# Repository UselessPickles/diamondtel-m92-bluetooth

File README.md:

# DiamondTel Model 92 Bluetooth Adapter

This is an electronics/microcontroller project for adapting a DiamondTel Model 92 Portable Cellular Telephone to work as a fully functional phone by routing calls through a modern cell phone via the Bluetooth Hands-Free Profile (HFP).

This project includes both a custom electronics circuit and custom microcontroller software.

**UPDATE**: A new version of this project is in development with custom PCBs that are completely hidden inside of the original car phone transceiver. See the [new-standalone-design branch](https://github.com/UselessPickles/diamondtel-m92-bluetooth/tree/new-standalone-design) of this project, but beware that documentation is not fully updated, and it is very much still in progress.

- [DiamondTel Model 92 Bluetooth Adapter](#diamondtel-model-92-bluetooth-adapter)
  - [About This Project](#about-this-project)
    - [TL;DR (with demo videos)](#tldr-with-demo-videos)
    - [The DiamondTel Model 92 Portable Cellular Telephone](#the-diamondtel-model-92-portable-cellular-telephone)
    - [Motivation / Goals](#motivation--goals)
    - [Project Forum Thread](#project-forum-thread)
    - [Discussion](#discussion)
    - [Documentation](#documentation)
    - [Media Coverage](#media-coverage)
  - [Basic Design](#basic-design)
    - [High Level Design Summary](#high-level-design-summary)
    - [Design Pros/Cons](#design-proscons)
  - [Compatibility](#compatibility)
    - [Vintage Mobile Phone](#vintage-mobile-phone)
    - [Paired Modern Cell Phone](#paired-modern-cell-phone)
  - [Build Your Own Bluetooth Adapter](#build-your-own-bluetooth-adapter)
  - [About the Author](#about-the-author)
  
## About This Project

### TL;DR (with demo videos)

I have an old car phone in my early 90's car. It's impossible to activate service for these old phones. I made the old car phone actually work like a real phone.

Click to view a YouTube video tour and demo of the complete car phone system with Bluetooth adapter:

You can find all videos I have created about this project in [this YouTube playlist](https://www.youtube.com/playlist?list=PLOlio4FadqvQEWHDXaJHlkvHigROk-RNV).

### The DiamondTel Model 92 Portable Cellular Telephone

The DiamondTel Model 92 Portable Cellar Telephone is a hybrid transportable/mobile (mobile, as in, "car phone") manufactured by Mitsubishi in the early 1990's. 

The phone used 1G analog cellular technology ([AMPS](https://en.wikipedia.org/wiki/Advanced_Mobile_Phone_System)), which has been discontinued in the US since 2008. As such, it is impossible to activate service for this phone. 

See the contents and README in the `telephone` directory for more details.

### Motivation / Goals

I want my DiamondTel Model 92 telephone to actually work as a phone, and not just by hacking an off-the-shelf Bluetooth headset into the phone's handset. I want the complete experience of the phone to be nearly indistinguishable from how the phone was originally intended to behave:

- Incoming calls should cause the phone to ring, and I should be able to answer incoming calls as expected (press the "SEND" button or pick up the handset).
- I should be able to place outgoing calls by dialing a number on the handset then pressing "SEND".
- The handset display should work and display all relevant information just like the original phone did.
- Sounds should be accurate to the original phone (button press sounds, ringtone, status alert sounds, etc.).
- A majority of the phone's original features should be fully functional (e.g., volume controls, call timer, quick dial presets, contacts directory with names and numbers).

### Project Forum Thread

I have documented my entire journey with this project in an [Electro-Tech-Online.com forum thread](https://www.electro-tech-online.com/threads/making-a-bluetooth-adapter-for-a-car-phone-from-the-90s.162764/).

Browse this thread if you are interested in all the technical details of how I reverse-engineerd how the DiamondTel Model 92 telephone works, how I fumbled my way through the electronics/hardware (with much appreciated assistance), and various problems I had to solve.

Subscribe to this thread if you want to be notified of significant updates about this project.

### Discussion

Do you have something to ask/say about this project? You can reach out to me in [this Gitter chat room](https://gitter.im/UselessPickles/diamondtel-m92-bluetooth).

### Documentation

There's too much information to put in one README. Most directories of this project have a README containing relevant documentation for that portion of the project. So explore the directory structure and use the READMEs to get familiar with it.

### Media Coverage

There's been a bit of media coverage of my project. Here's some links:

- [Hackaday](https://hackaday.com/2023/04/13/custom-bluetooth-adapter-brings-1990s-car-phone-back-online/)
- [Jalopnik](https://jalopnik.com/vintage-factory-car-phone-connects-to-smartphone-1850329711)
- [CarBuzz](https://carbuzz.com/news/genius-turns-30-year-old-mitsubishi-3000gt-into-a-smartphone)
- Hagerty: Piston Slap
    - [Part 1](https://www.hagerty.com/media/advice/piston-slap/piston-slap-new-tricks-for-an-old-car-phone-part-iv/)
    - [Part 2](https://www.hagerty.com/media/advice/piston-slap/piston-slap-new-tricks-for-an-old-car-phone-part-v/)
- [Japanese Nastolgic Car](https://japanesenostalgiccar.com/mitsubishi-3000gt-car-phone-functional-with-iphone-bluetooth/)
- [Hackster.io](https://www.hackster.io/news/jeff-lau-s-open-source-bluetooth-adapter-brings-a-mitsubishi-carphone-classic-back-from-the-dead-383864868529)
- [The Drive](https://www.thedrive.com/news/clever-collector-mods-mitsubishi-3000gt-car-phone-to-work-like-an-iphone)

## Basic Design

### High Level Design Summary

- A custom Bluetooth adapter connects inline between the DiamondTel Model 92 handset and transceiver.
- The transceiver provides its power supply and power on/off functionality to the Bluetooth adapter.
    - Power supply, ground, and handset power button connection is passed through the Bluetooth adapter between the handset and transceiver.
    - When the transceiver powers on, the Bluetooth adapter also powers on via the same power supply that powers the handset.
- The Bluetooth adapter takes full control of the handset.
- The Bluetooth adapter fully implements all behavior that is experienced by interacting with the handset. Much of it is a replica of (or inspired by) the DiamondTel Model 92's original behavior.
- The Bluetooth adapter communicates with the transceiver to monitor the transceiver battery level.    
- There is no direct pass-through communication between the handset and transceiver.
    - As far as the transceiver knows, it simply powers up and remains in its default idle state at all times (except for when the Bluetooth adapter requests the battery level).
- The Bluetooth adapter pairs with a modern cell phone using the Bluetooth Hands-Free Profile (HFP). This Bluetooth connection is used to:
    - Monitor/display cell service status and signal strength, etc.
    - Handle incoming calls.
    - Send outgoing calls.
    
### Design Pros/Cons

Pros:

- Plug-n-play design - no modifications to the original phone.
- No separate power supply is needed.
- Can pair with practically any modern cell phone (no separate SIM card needed).
- The vintage mobile phone has the appearance of being a completely original and functioning phone (assuming that the Bluetooth adapter is hidden, which is easy when the phone is installed in a vehicle as a car phone).
- Full control of implementing any desired behavior (within limitations of the handset display/button capabilities, and within limitations of Bluetooth HFP), including functionality that was never available/possible on the original phone (e.g., Caller ID).

Cons:

- Requires a lot of custom software to replicate original DiamondTel Model 92 functionality as faithfully as possible (but that's OK with me; I'm a software engineer, and this is fun!).
- This is not a general design that will work with a wide range of vintage mobile phones.

## Compatibility

### Vintage Mobile Phone

Because this design relies on a direct wired interface with the handset and transceiver (using proprietary connections and digital communications), it has very limited compatibility. As of now, this project is only known to work with the following vintage mobile phones:

- DiamondTel Model 92
- Mitsubishi Model 1500

### Paired Modern Cell Phone

Any modern cell phone that supports Bluetooth Hands-Free Profile (HFP) _should_ (in theory) be able to pair with the Bluetooth adapter and work properly. I have a very limited selection of phones to test with, so I can't make any guarantees.

These are the modern cell phones performed at least some basic testing with:

- Apple iPhone 8
- Apple iPhone SE
- Apple iPhone 14
- Google Pixel 3 XL

## Build Your Own Bluetooth Adapter

I don't have a complete detailed step-by-step guide, but all the information needed to build your own Bluetooth adapter should be here.

Some prerequisites:
- Soldering skills. There's a lot of soldering if you build a prototype like mine.
- Attention to detail. There are countless opportunities to make mistakes if you are not careful, and it may be a very long time and a large amount of effort before you discover that something is not working correctly.
- Basic understanding of electronics and how to use tools like a multimeter and an oscilloscope to verify your work along the way or troubleshoot when something doesn't work because you probably made a mistake while soldering everything together (I made several small mistakes while building my prototype that I had to troubleshoot and fix).
- Computer/software competency. You will need to use a variety of software tools to load configuration and code onto the Bluetooth module and the microcontroller. These are not the most user-friendly software tools.

Basic steps for building a Blutooth adapter:
1. See the `/hardware` directory README and the VeroRoute circuit layout to find all the components/parts you'll need. VeroRoute can give you a BOM list of components and quantities of most components. The README has some additional details of other items/components used in my prototype.
1. See the `/bluetooth/config` directory README for details about how to update/configure the BM62 Bluetooth module. If you use the same breadboard adapter as I did for the BM62, and you use female header sockets on your circuit, then you can easily update/configure the BM62 at any time either before or after the rest of the circuit is put together. If you want to solder the BM62 directly into your circuit, then you need to come up with a plan for how you will update/configure the BM62.
1. Build the hardware based on the information found in the `/hardware` directory/README.
1. Build the microcontroller software in the `/microcontroller/DiamondTelM92Bluetooth.X` directory and load it onto the microcontroller, using [MPLAB X](https://www.microchip.com/en-us/tools-resources/develop/mplab-x-ide) and a [PICKIT 4](https://www.microchip.com/en-us/development-tool/PG164140) or equivalent tool. Use the internet to learn how to do this if you don't already know.
1. See the `/operating_instructions` directory README for information about how to use the Bluetooth adapter.

## About the Author

I'm a software engineer with primary professional expertise in front-end web app development, but I've also played around with some basic electronics and microcontoller programming for fun. This is by far my most ambitious electronics/microcontroller project. 

The electronics side of things is my weakness, and I've relied on quite a bit of assistance from people that know electronics better than me to get this far. If you know electronics, and think I did something stupid or unnecessary in my circuit design, then you're probably right! Please file an issue against this project if you have recommendations!

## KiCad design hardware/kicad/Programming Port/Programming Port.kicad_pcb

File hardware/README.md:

# Bluetooth Adapter Hardware

This directory contains information about the hardware portion of the DiamondTel Model 92 Bluetooth adapter.

NOTE: The Bluetooth Module, Microcontroller, and Telephone all have dedicated top-level directories with relevant technical information, datasheets, and much more. This directory focuses more on combining all the components together into the bluetooth adapter hardware.

- [Bluetooth Adapter Hardware](#bluetooth-adapter-hardware)
  - [Basic Circuit Design](#basic-circuit-design)
  - [Major Circuit Components](#major-circuit-components)
    - [Microcontroller (PIC18F27Q43)](#microcontroller-pic18f27q43)
    - [Bluetooth Module (BM62)](#bluetooth-module-bm62)
    - [Hands-Free Microphone Jack (STX3120)](#hands-free-microphone-jack-stx3120)
    - [Analog Switches (MAX4619)](#analog-switches-max4619)
    - [Op Amp (NJU7031)](#op-amp-nju7031)
    - [Low-Pass Filter](#low-pass-filter)
    - [Digital Potentiometer (MCP4151)](#digital-potentiometer-mcp4151)
    - [Differential Audio Driver (INA105)](#differential-audio-driver-ina105)
    - [5V Voltage Regulator (L7805CV)](#5v-voltage-regulator-l7805cv)
    - [Negative Voltage Converter (TL7660)](#negative-voltage-converter-tl7660)
  - [Detailed Circuit Diagrams](#detailed-circuit-diagrams)
  - [Prototype Board Layout](#prototype-board-layout)
  
## Basic Circuit Design

This is a simplified component diagram of the bluetooth adapter circuit. Many details of the circuit (power, ground, voltage biasing, supporting components, etc.) are omitted for clarity of understanding the big picture of how the major components interact with each other.

[TODO]

## Major Circuit Components

This is a summary of all the major components of the bluetooth adapter circuit.

Datasheets for most components can be found in `datasheets` directory.

NOTE: Not all of these components are represented in the [Basic Circuit Design](#basic-circuit-design) diagram.

### Microcontroller (PIC18F27Q43)

This is what integrates everything together and implements all the interactive phone behavior.

See the top-level `/microcontroller` directory and the contained MPLAB project directory for more details.

### Bluetooth Module (BM62)

This handles all the Bluetooth communication with a modern cell phone, as commanded by the Microcontroller.

See the top-level `/bluetooth` directory for more details.

### Hands-Free Microphone Jack (STX3120)

This 3.5mm audio jack is used for connecting an external microphone for hands-free conversation.

The jack includes disconnect switches that are used to trigger a digital input to the MCU, indicating when
an external microphone is connected.

### Analog Switches (MAX4619)

This component is a set of 3 analog SPDT switches in one component. This is used to allow the Microcontroller to control the routing of audio:

- Choose between sending incoming voice audio or MCU-generated sounds to the Handset.
- Choose between sending the handset microphone audio or external hands-free microphone audio to the Bluetooth Module.
- Disable the microphone connection to the Bluetooth Module to temporarily "mute" the microphone while the MCU is generating sound output to the Handset.

### Op Amp (NJU7031)

This Op Amp is used to buffer the raw DAC sound output from the Microcontroller before passing it through any further circuitry.

Another is used to amplify the incoming audio from the external hands-free microphone jack.

### Low-Pass Filter

A single stage RC network is used to *partially* smooth out the 10KHz sample rate DAC audio output from the Microcontroller.

The original car phone appears to intentionally retain some high-frequency overtones in the sounds it produces. This gives the sounds a more harsh/piercing sound quality, which probably helps ensure the ringer is heard when there's an incoming call.

I similarly intentionally setup the low-pass filter to only partially smooth over the sharp corners of the DAC output. It's not an exact match to the original phone, but it sounds similar enough.

### Digital Potentiometer (MCP4151)

This digital potentiometer allows the Microcontroller to control the volume of audio output the the Handset.

### Differential Audio Driver (INA105)

A pair of INA105 precision unity gain opamps is used to produce [differential](https://en.wikipedia.org/wiki/Differential_signalling) audio output to the Handset. One is setup as unity gain, while the other is setup as inverting unity gain.

NOTE: This component requires a +5V and -5V power supply.

### 5V Voltage Regulator (L7805CV)

This voltage regulator produces a +5V power supply for the circuit. The ~12V power supply from the Transceiver is used as input.

### Negative Voltage Converter (TL7660)

This component produces a -5V power supply from the main +5V power supply. This is necessary for the [Differential Audio Driver](#differential-audio-driver-ina105).

## Detailed Circuit Diagrams

See the KiCad projects in the `kicad` directory for complete schematics and PCB layouts.

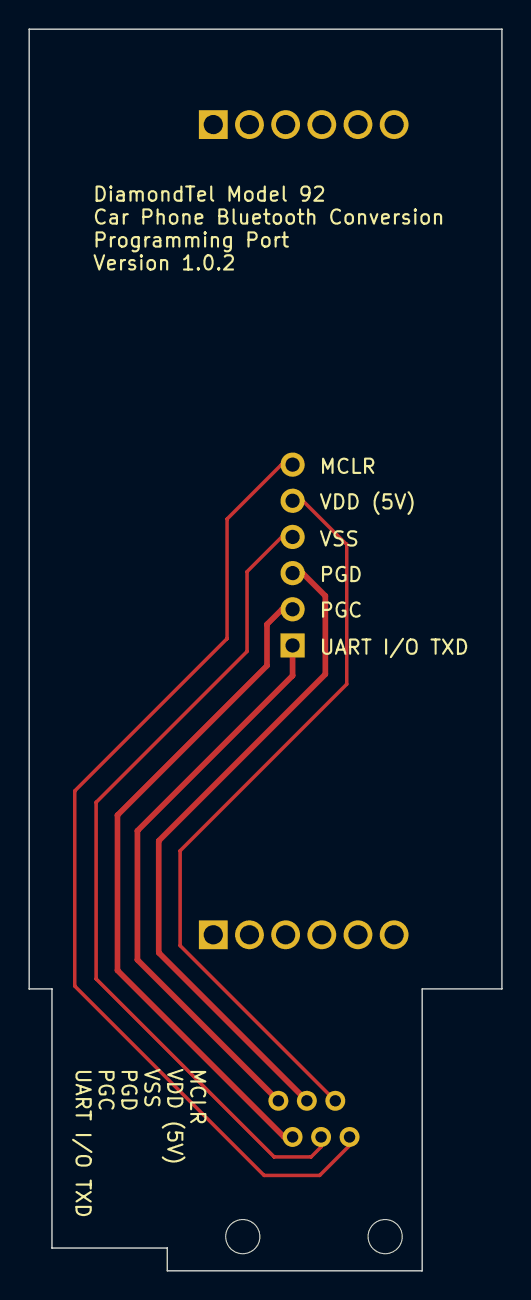
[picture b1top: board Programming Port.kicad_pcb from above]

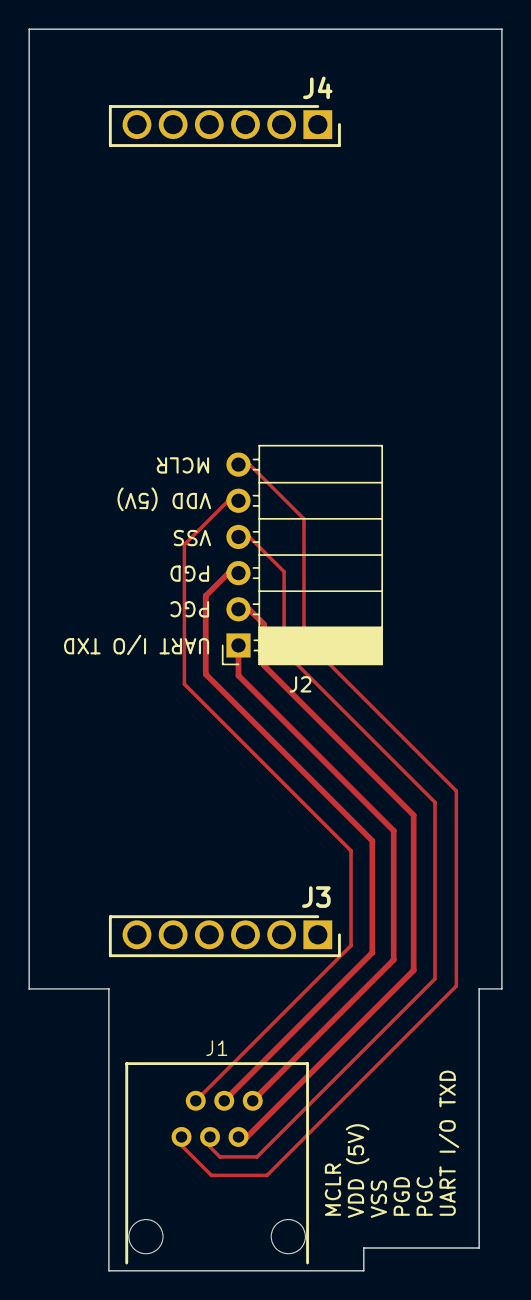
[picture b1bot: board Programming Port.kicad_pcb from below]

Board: 2 copper layers, 33.2 x 87.2 mm, 4 parts (4 on the bottom side), 6 nets.

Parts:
J1: TM5RE1-66
J2: PPTC061LGBN-RC; PinSocket_1x06_P2.54mm_Horizontal
J3, J4: PPTC061LFBN-RC; RHDR6W80P0X254_1X6_1574X254X870P_1MM_SPACER

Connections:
unnamed: J1.6, J2.1
unnamed: J1.5, J2.2
unnamed: J1.4, J2.3
unnamed: J1.3, J2.4
unnamed: J1.2, J2.5
unnamed: J1.1, J2.6

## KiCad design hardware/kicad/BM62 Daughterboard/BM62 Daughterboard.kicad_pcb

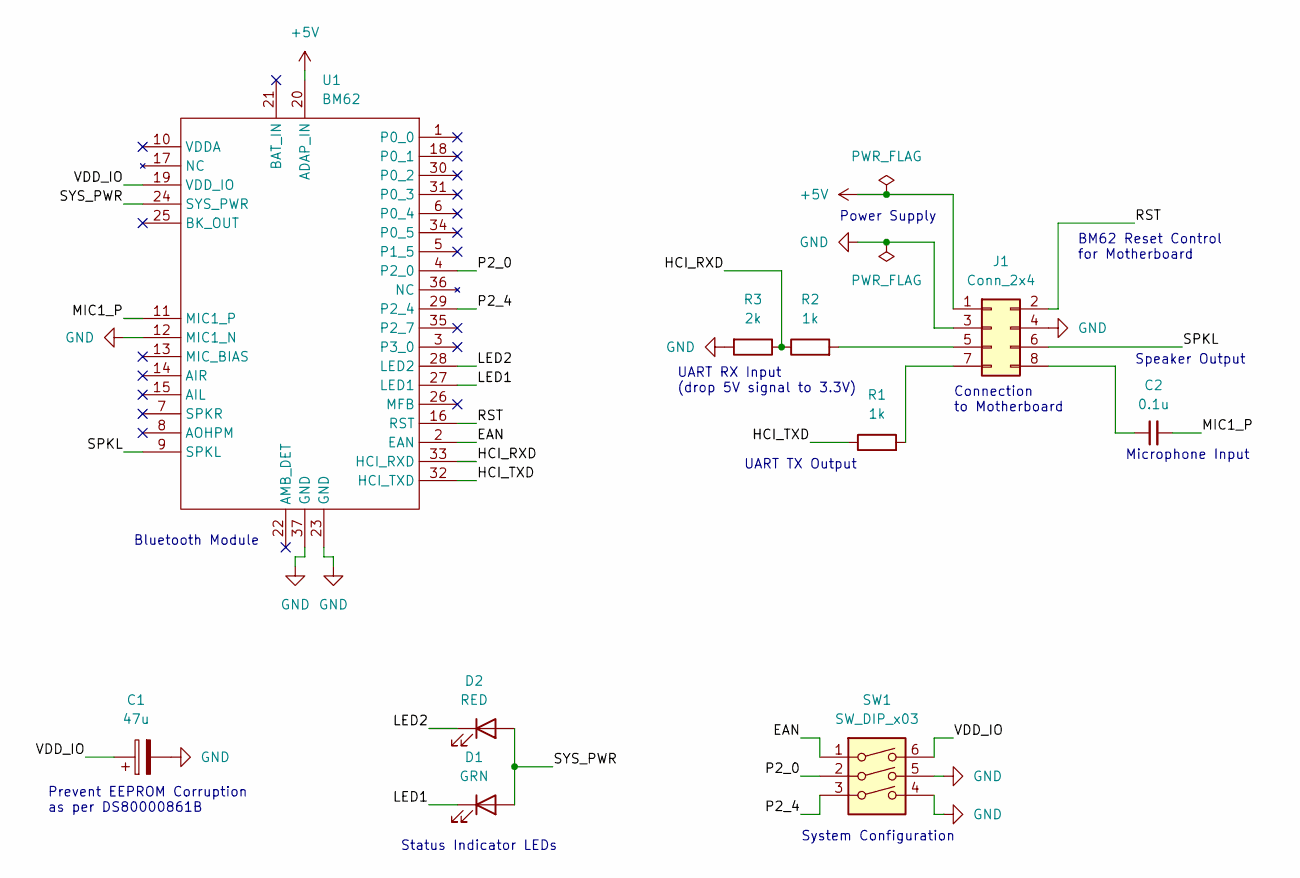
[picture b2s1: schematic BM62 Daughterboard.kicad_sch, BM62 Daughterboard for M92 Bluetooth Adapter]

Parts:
C1: 47u; CP_Elec_6.3x5.4; Manufacturer_Part_Number EXV476M016A9GAA; Mouser Part Number 80-EXV476M016A9GAA
C2: 0.1u; C_1206_3216Metric_Pad1.33x1.80mm_HandSolder; Manufacturer_Part_Number C1206C104J4HACTU; Mouser Part Number 80-C1206C104J4HACTU
D1: GRN; LED_1206_3216Metric_Pad1.42x1.75mm_HandSolder; Manufacturer_Part_Number HSME-C150; Mouser Part Number 630-HSME-C150
D2: RED; LED_1206_3216Metric_Pad1.42x1.75mm_HandSolder; Manufacturer_Part_Number HSMC-C150; Mouser Part Number 630-HSMC-C150
J1: Conn_2x4; PinHeader_2x04_P2.54mm_Horizontal; Manufacturer_Part_Number 90122-0124; Mouser Part Number 538-90122-0124
R1, R2: 1k; R_1206_3216Metric_Pad1.30x1.75mm_HandSolder; Manufacturer_Part_Number CR1206-FX-1001ELF; Mouser Part Number 652-CR1206FX-1001ELF
R3: 2k; R_1206_3216Metric_Pad1.30x1.75mm_HandSolder; Manufacturer_Part_Number CR1206-FX-2001ELF; Mouser Part Number 652-CR1206FX-2001ELF
SW1: SW_DIP_x03; DS04254103BKSMT; Manufacturer_Part_Number DS04-254-1-03BK-SMT; Mouser Part Number 490-DS04254103BK-SMT
U1: BM62; Microchip BM62; Manufacturer_Part_Number BM62SPKS1MC2-0001AA; Mouser Part Number 579-62SPKS1MC20001AA

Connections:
+5V: J1.1, U1.20 (ADAP_IN)
/EAN: SW1.1, U1.2 (EAN)
/HCI_RXD: R2.1, R3.1, U1.33 (HCI_RXD)
/HCI_TXD: R1.1, U1.32 (HCI_TXD)
/LED1: D1.1 (K), U1.27 (LED1)
/LED2: D2.1 (K), U1.28 (LED2)
/MIC1_P: C2.2, U1.11 (MIC1_P)
/P2_0: SW1.2, U1.4 (P2_0)
/P2_4: SW1.3, U1.29 (P2_4)
/RST: J1.2, U1.16 (RST)
/SPKL: J1.6, U1.9 (SPKL)
/SYS_PWR: D1.2 (A), D2.2 (A), U1.24 (SYS_PWR)
/VDD_IO: C1.1, SW1.6, U1.19 (VDD_IO)
GND: C1.2, J1.3, J1.4, R3.2, SW1.4, SW1.5, U1.12 (MIC1_N), U1.23 (GND), U1.37 (GND)
unnamed: J1.5, R2.2
unnamed: J1.7, R1.2
unnamed: C2.1, J1.8

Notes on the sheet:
Status Indicator LEDs
BM62 Reset Control for Motherboard
Prevent EEPROM Corruption as per DS80000861B
System Configuration
UART TX Output
Connection to Motherboard
Power Supply
Bluetooth Module
Speaker Output
Microphone Input
UART RX Input (drop 5V signal to 3.3V)

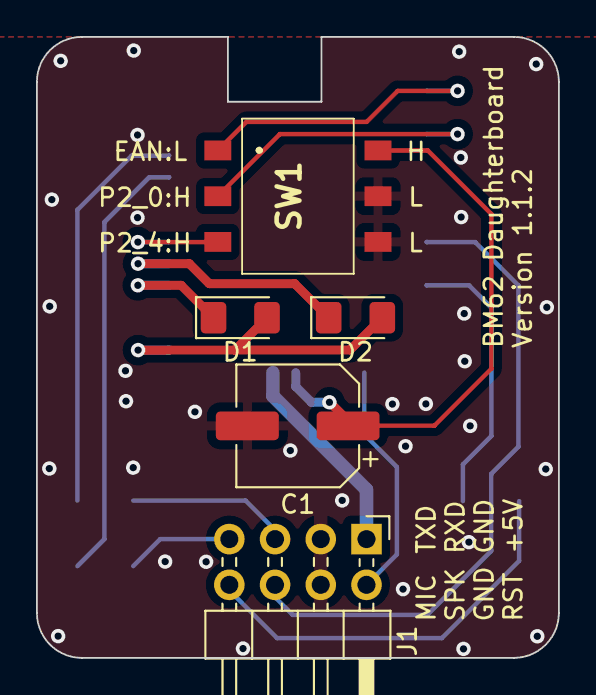
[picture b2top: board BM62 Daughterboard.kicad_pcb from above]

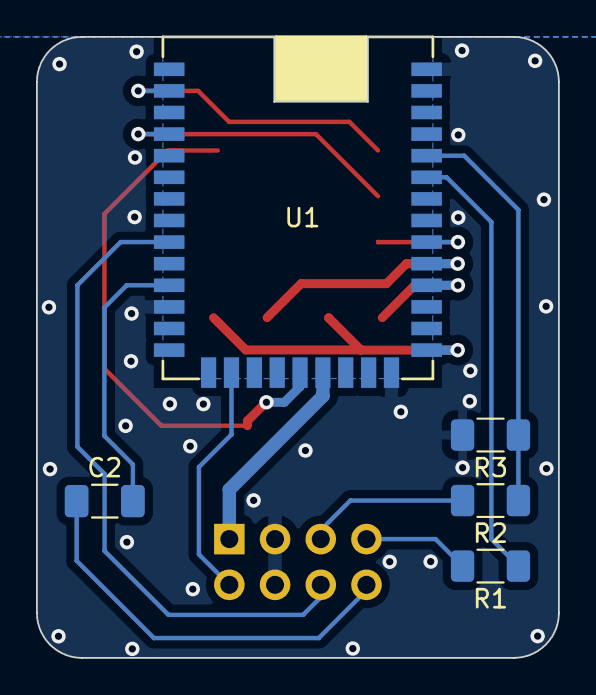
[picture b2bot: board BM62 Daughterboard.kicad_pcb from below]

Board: 2 copper layers, 29.0 x 34.5 mm, 10 parts (5 on the bottom side), 17 nets.

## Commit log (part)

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2022-12-10 Initial commit of MPLAB project
2022-12-11 Initial commit of microcontroller project documentation
2022-12-11 Add README for bluetooth module docs
2022-12-12 Fix spacing in the basic component diagram
2022-12-12 Fix a README typo
2022-12-12 Add breadboard prototype photos to README and update compatible phones list
2022-12-13 Change README terminology and improve basic design diagram
2022-12-16 Add handset UART spreadsheet, and add sound frequencies to README
2022-12-17 Rename microcontroller datasheet file
2022-12-17 Rename a datasheet file
2022-12-17 Clean up the hardware README
2022-12-17 Update Bluetooth config to enable Rx indicator
2022-12-19 Disable BM62 UART CPU Idle Mode
    BM62 UART CPU Idle Mode seems to cause glitches in incoming phone call audio.
2022-12-20 Update MCU software README to explain the use of the FVR peripheral.
2022-12-21 Document HANDSET_EventHandler typedef
2022-12-21 Move firmware files into the bluetooth config directory
2022-12-22 More bluetooth config readme improvements and a firmware version typo fix
2022-12-22 Replace BM62 UART command set documentation with new version
2022-12-23 Improve factory reset to completely wipe out all data
    Added support writing a repeating value to EEPROM asynchronously.
    Added EEPROM_AsyncErase() function that asynchronously writes 0xFF to every address.
    Use new EEPROM_AsyncErase() function for factory reset.
    Remove unnecessary BT Disconnect call during factory reset.
    Remove STORAGE_ResetToDefaults() function.
    Fix possible EEPROM writing bug? Wait for NVMCON0bits.GO to reset between reading and writing.
2022-12-24 Cleanup and documentation of volume_adjust code
2022-12-24 Fix code comment typo
2022-12-25 Fix off-by-one error when looking up credit card memory storage for sending as DTMF
2022-12-29 Small cleanup
2022-12-29 Simplified main.c to remove awkward dependencies
    Simplified main.c to so that it only initializes the system and initializes/runs the main "app" module (app.c). All application subsystems/submodules are now initialized and executed from within the 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
2022-12-29 Rename all Timer_Tick functions to Timer_Interrupt to clarify that it is interrupt code
2022-12-30 Add high score player initials feature to Tetris
    User can now enter their initials when they get a high score in Tetris. The initials are displayed along with the high score.
2023-01-02 Update/add file-level comments to all source code for consistency
2023-01-04 Regenerate MCC output
2023-01-05 Adjust cadence of standard ringtone to match original phone
    Original phone's ringer cadence is now known to be 1 second on, 3 seconds off, as determined by using a mobile service tester to simulate an incoming call.
2023-01-05 Update call time warning beep target and volume mode
    Update call time warning beep target and volume mode to be consistent with the behavior of the original phone.
2023-01-06 Update telephone README with more info about sound frequencies
2023-01-06 Remove incorrect ringtone info from telephone README
    I was mistaken in my understanding of the ringtones. The "harsh" ringtone is the only authentic original ringtone. The description of the "smooth" ringtone variant is removed.
2023-01-14 Various typo fixes
2023-01-15 Improve outgoing call and call timer behavior again
    Previous update to outgoing call and call timer behavior wasn't quite correct according to the original phone behavior.
    Updates/improvements to call timer behavior:
    - If call timer was displayed when "navigating" to another screen, the call timer is now redisplayed upon "returning", even if the number input is populated.
    - Call timer now displays during a call immediately upon clearing out the current number.
    - After hiding the call display, clearing out the number input, then hiding the call timer again, the call timer will be redisplayed again automatically after "navigating' to another screen then retu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
    Big improvement to outgoing
2023-01-17 Reorganize DTMF AT command code
    - Moved DTMF AT command code from app.c to atcmd.c
    - Introduce 100ms delay between successful completion of a DTMF command and the queueing of the next DTMF command (sounds less chaotic/rushed)
2023-02-01 Introduce TIMEOUT_StartOrContinue() function
2023-02-01 This was supposed to be part of the previous commit
2023-02-12 Improve compatibility with the Hands-Free Controller
    * Disable Caller ID when in "vehicle mode", because caller ID breaks out of hands-free "incoming call" mode.
    * Send specific sequences of commands that the Hands-Free Controller expects to signal the start and end of an incoming call.
    * Get rid of the flashing IN USE indicator for Call Waiting, because it would switch the Hands-Free Controller in/out of "in call" mode. Need to come up with a replacement indication later.
2023-02-12 Fix bug with Call Waiting and Hands-Free Controller
    After answering or ignoring an incoming call waiting (while already in an active call), the Hands-Free Controller incorrectly believed that it was no longer "in a call". The command for enabling the 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
2023-02-17 Add datasheet for audio jack (to be used for external mic input)
2023-02-22 Add external power detection, external mic detection, and OEM hands-free support configuration
    * Removed the manual "CARRIED" vs "VEHICLE" mode selection and replaced with automatic detection of external power (inferred from back-light on/off commands received from the transceiver). Handset is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
    * Added external microphone connection detection via a digital input pin.
    * Added a new programmable setting to enable OEM Hands-Free integration support. When enabled, and an external microphone is connected, then Caller ID is automatically disabled to prevent interferenc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
2023-02-25 More circuit component diagram alignment tweaks
2023-03-04 Fix initial state of SOUND module
    Initial "speaker mode" was incorrectly IDLE instead of NONE. NONE is necessary initially to ensure a proper delay between turning on the handset audio and beginning to produce sound when initializing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
2023-03-04 MCC file changes
2023-03-05 Initial commit of partial Operating Instructions
    Only includes clarification of original DiamondTel Model 92 functionality support. Much more to be added.
2023-03-08 Update circuit layout
2023-03-19 Change FVR output from 2x to 4x to account for hardware change
2023-03-20 Circuit layout tweaks
2023-03-21 Adjust startup sequence timing to match original phone better
2023-03-22 Circuit layout adjustment
2023-03-22 Fix hardware README leftover mention of no longer used INA105 component
2023-03-22 Update MCU project README to match new pin assignments
2023-03-23 Add more functionality coverage to the operating instructions
2023-03-24 Update capacitor values for MCU sound output low-pass filter and coupling
2023-03-24 Re-display paired phone name after resetting pairing memory to confirm thata phone is no longer paired
2023-04-05 Update hardware README with photos of prototype board
2023-04-12 Update main README to reference the new video of a complete tour/demo
2023-04-21 Remove "Under Construction" from README
    There's room to improve, but this repo is "complete enough" for now to stop claiming it is "under construction".
2023-04-26 Fix README typos
2023-06-01 Fix broken link in BM62 config README
2023-12-04 Fix bug: Unable to reject incoming call
2024-01-21 Rework MCU config and code for new standalone hardware design
    MCU config and code is reworked for new hardware design that eliminates interface with the original car phone transceivers and instead manages its own power on/off behavior, battery level detection, 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
2024-01-22 Swap UART3 TX/RX pin assignments for better PCB layout
2024-01-23 Add minimum delay between low battery warning and low voltage power-off
2024-01-26 Add KiCad lock files to gitignore
2024-01-27 Remove unnecessary interrupt disable/enable code when putting the MCU to sleep
    Disabling interrupts was only necessary before I added code to disable all peripherals I didn't want operating during sleep.
2024-01-28 Update LED part info for BM62 Daughterboard
2024-02-05 Create new symbol/footprint for original 8-pin header on transceiver PCB
2024-02-09 Remove hack to fake 100% battery level, because I got a new MCU
    I have a new MCU that can properly take ADC readings of the battery voltage, so the logic can work in terms of real battery levels now.
2024-02-10 Update circuit/PCB to use different power supply/switching components
    * Use more efficient 5V regulator.
    * Use load switch ICs instead of reed switch relays for power switching.
    * Swapped MCU pins for battery voltage detect and power switching for better PCB layout.
2024-02-13 Update default Bluetooth name
    Default Bluetooth name is changed to a more generic value: "Car Phone"
2024-02-23 BM62 daughterboard adjustment to connector ground pins
2024-03-01 Minor circuit and PCB layout adjustments
    * Enable quick output discharge feature of both load switches.
    * Change a decoupling cap from 1uF to 0.1uF for consistency.
    * Fix incorrect labeling on the PCB of the BT module connector pinout.
2024-03-16 Fix bug: "call ended" sound would play even when call was ended from the car phone
2024-03-19 Update main README to describe new Bluetooth adapter design
2024-04-25 BM62 Daughterboard fixes
    * Fixed some pin assignments that I must have messed up previously
    * Added JLCPCB part numbers for parts on the bottom side
2024-12-31 Minor BM62 daughterboard PCB improvements
    * Center/align some components.
    * Setup proper copper exclusion in the BM62 footprint.
    * Increase width of several ground connections.
2025-01-07 Change microphone jack footprint to use oval holes/pads
2025-01-17 Add MCU power-on condition console logging
    When the MCU powers on, log the power-on conditions. Also some minor cleanup documentation fixes.
2025-01-19 Update MCU project README with new I/O UART baud rate
2025-01-24 Update main README about new standalone design in progress
